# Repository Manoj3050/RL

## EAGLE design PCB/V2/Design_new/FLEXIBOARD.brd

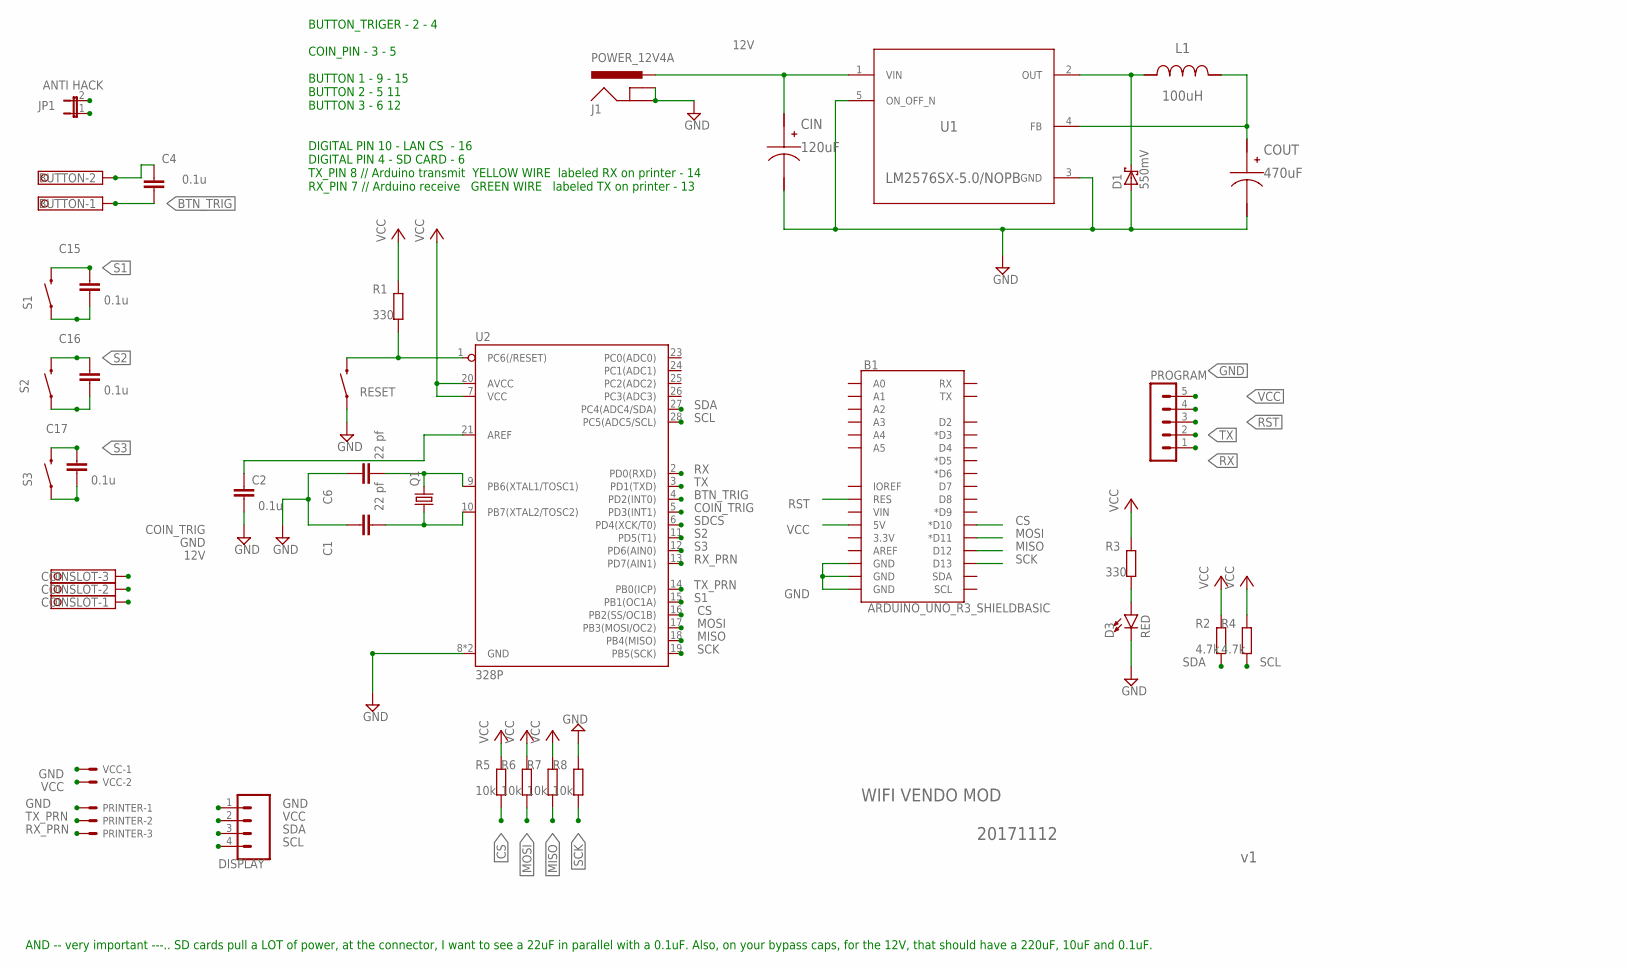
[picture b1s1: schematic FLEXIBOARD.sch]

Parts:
B1: ARDUINO_UNO_R3_SHIELDBASIC; UNO_R3_SHIELD
BUTTON: TERMINAL-BLOCK-3.5MM-2-PIN-LONG-PAD; TERMINAL-BLOCK-2-PIN-3.5MM-LONG-PAD
C1, C6: 22 pf; C050-024X044
C2, C4, C15, C16, C17: 0.1u; C050-024X044
CIN: 120uF; CAPSMT_62_F61_T
COINSLOT: TERMINAL-BLOCK-3.5MM-3-PIN-LONG-PAD; TERMINAL-BLOCK-3-PIN-3.5MM-LONG-PAD
COUT: 470uF; SM_RADIAL_G_T
D1: 550mV; C4111-15
D3: RED; LED_5MM
DISPLAY: M04PTH; 1X04
J1: POWER_12V4A; POWER_JACK_PTH
JP1: ANTI HACK; SJ_2S-NO
L1: 100uH; PM2110
PRINTER: JST-XH-03-PIN-LONG-PAD; JST-XH-03-PACKAGE-LONG-PAD
PROGRAM: MA05-1
Q1: CRYSTALSM49; SM49
R1, R3: 330; 0204/7
R2, R4: 4.7k; 0204/7
R5, R6, R7, R8: 10k; 0204/7
RESET: SWITCH-MOMENTARY-2PTH_EZ; TACTILE-PTH-EZ
S1, S2, S3: SWITCH-MOMENTARY-2PTH_EZ; TACTILE-PTH-EZ
U1: LM2576SX-5.0/NOPB; KTT0005B_T
U2: 328P; DIP28
VCC: JST-XH-02-PIN-LONG-PAD; JST-XH-02-PACKAGE-LONG-PAD

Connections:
12V: CIN.P$1 (+), COINSLOT.1, J1.PWR, U1.1 (VIN)
BTN_TRIG: BUTTON.1, C4.2, U2.4 (PD2(INT0))
COIN_TRIG: COINSLOT.3, U2.5 (PD3(INT1))
CS: B1.D10 (*D10), R5.1, U2.16 (PB2(SS/OC1B))
GND: B1.GND@0 (GND), B1.GND@1 (GND), B1.GND@2 (GND), BUTTON.2, C1.1, C2.2, C4.1, C6.1, C15.2, C16.2, C17.2, CIN.P$2 (-), COINSLOT.2, COUT.P$2 (-), D1.A, D3.K (C), DISPLAY.1, J1.GND, J1.GNDBREAK, PRINTER.1, PROGRAM.5, R8.2, RESET.1, S1.1, S2.1, S3.1, U1.3 (GND), U1.5 (ON_OFF_N), U2.8 (GND), U2.22 (GND), VCC.1
MISO: B1.D12, R7.1, U2.18 (PB4(MISO))
MOSI: B1.D11 (*D11), R6.1, U2.17 (PB3(MOSI/OC2))
unnamed: C6.2, Q1.2, U2.9 (PB6(XTAL1/TOSC1))
unnamed: C1.2, Q1.1, U2.10 (PB7(XTAL2/TOSC2))
unnamed: D1.C, L1.1, U1.2 (OUT)
unnamed: D3.A, R3.1
unnamed: C2.1, U2.21 (AREF)
unnamed: COUT.P$1 (+), L1.2, U1.4 (FB)
RST: B1.RES, PROGRAM.3, R1.1, RESET.3 (2), U2.1 (PC6(/RESET))
RX: JP1.2, PROGRAM.1, U2.2 (PD0(RXD))
RX_PRN: PRINTER.3, U2.13 (PD7(AIN1))
S1: C15.1, S1.3 (2), U2.15 (PB1(OC1A))
S2: C16.1, S2.3 (2), U2.11 (PD5(T1))
S3: C17.1, S3.3 (2), U2.12 (PD6(AIN0))
SCK: B1.D13, R8.1, U2.19 (PB5(SCK))
SCL: DISPLAY.4, R4.1, U2.28 (PC5(ADC5/SCL))
SDA: DISPLAY.3, R2.1, U2.27 (PC4(ADC4/SDA))
SDCS: U2.6 (PD4(XCK/T0))
TX: JP1.1, PROGRAM.2, U2.3 (PD1(TXD))
TX_PRN: PRINTER.2, U2.14 (PB0(ICP))
VCC: B1.5V, DISPLAY.2, PROGRAM.4, R1.2, R2.2, R3.2, R4.2, R5.2, R6.2, R7.2, U2.7 (VCC), U2.20 (AVCC), VCC.2

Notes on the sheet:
WIFI VENDO MOD
20171112
SCL
BUTTON_TRIGER - 2 - 4 COIN_PIN - 3 - 5 BUTTON 1 - 9 - 15 BUTTON 2 - 5 11 BUTTON 3 - 6 12 DIGITAL PIN 10 - LAN CS - 16 DIGITAL PIN 4 - SD CARD - 6 TX_PIN 8 // Arduino transmit YELLOW WIRE labeled RX on printer - 14 RX_PIN 7 // Arduino receive GREEN WIRE labeled TX on printer - 13
AND -- very important ---.. SD cards pull a LOT of power, at the connector, I want to see a 22uF in parallel with a 0.1uF. Also, on your bypass caps, for the 12V, that should have a 220uF, 10uF and 0.1uF.

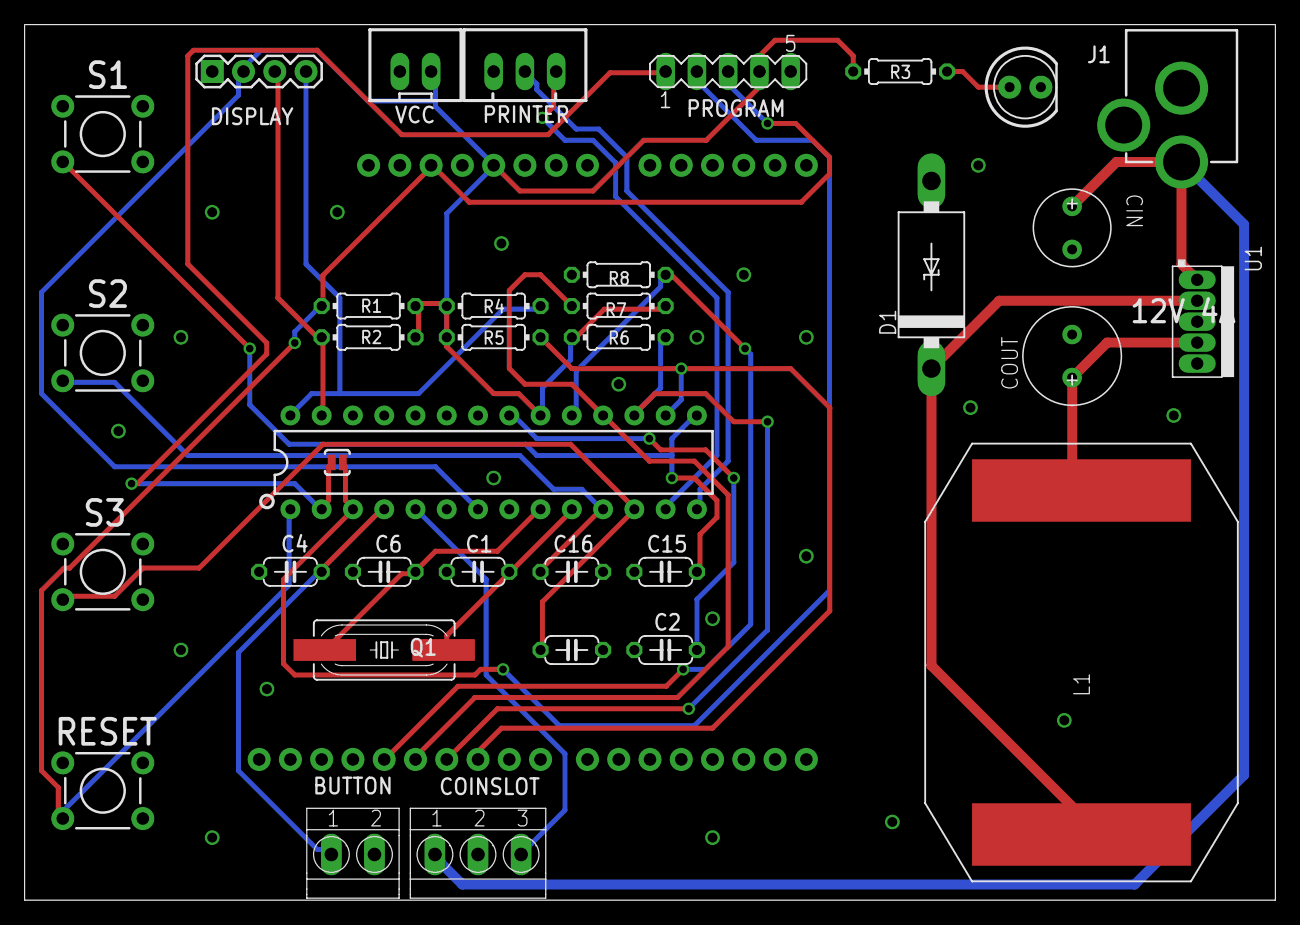
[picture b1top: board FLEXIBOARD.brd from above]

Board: 2 copper layers, 101.6 x 71.1 mm, 36 parts (1 on the bottom side), 25 nets.

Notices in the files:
parts and their libraries:
SparkFun-Electromechanical: Licensing: Creative Commons ShareAlike 4.0 International - https://creativecommons.org/licenses/by-sa/4.0
m-pad-2.1: License : GNU General Public License version 2 (see bottom)
